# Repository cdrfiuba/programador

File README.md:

# Programador del Club de Robótica

El club cuenta con varios programadores ISP.

Cada programador cuenta con dos conexiones:
* Target (targ)
    - La conexión más usada. Sirve para programar un microcontrolador externo.
* ISP
    - Sirve para programar el programador (usualmente usando otro programador del club).
      De esta forma un programador sirve para crear más programadores.

## Conexiones

Cada puerto cuenta con 6 pines conectados a un cable plano:

- VCC (usualmente +5V que vienen de la conexión USB)
- GND
- SCK Señal de clock.
- RESET Permite "apagar" el microcontrolador y programarlo por SPI. De esa forma los demás pines pueden ser usados para otras tareas cuando el microcontrolador no está siendo programado.
- MISO (master-in slave-out)<sup>1</sup> Datos del microcontrolador al programador.
- MOSI (master-out slave-in)<sup>1</sup> Datos del programador al microcontrolador.

<sup>1 Nota: SIMO y SOMI suelen ser nombres más simpáticos pero menos usados.</sup>

La ubicación de cada pin en el puerto se muestra a continuación

## [Wiki](https://github.com/cdrfiuba/programador/wiki)

En la [Wiki](https://github.com/cdrfiuba/programador/wiki) de este repositorio se detalla la construcción de un programador como su uso.

- [Programador del Club de Robótica](https://github.com/cdrfiuba/programador/wiki#programador-del-club-de-rob%C3%B3tica)
  - [¿Cómo armar el programador?](https://github.com/cdrfiuba/programador/wiki#c%C3%B3mo-armar-el-programador)
    - [Versión 1.8](https://github.com/cdrfiuba/programador/wiki#versi%C3%B3n-18)
    - [Versión 1.7](https://github.com/cdrfiuba/programador/wiki#versi%C3%B3n-17)
    - [Versión 1.6](https://github.com/cdrfiuba/programador/wiki#versi%C3%B3n-16)
  - [Lista de Materiales](https://github.com/cdrfiuba/programador/wiki#lista-de-materiales)
    - [Versión 1.6 a 1.8:](https://github.com/cdrfiuba/programador/wiki#versi%C3%B3n-16-a-18)
      - [Lista de materiales a soldar](https://github.com/cdrfiuba/programador/wiki#lista-de-materiales-a-soldar)
      - [Lista de materiales para comprar](https://github.com/cdrfiuba/programador/wiki#lista-de-materiales-para-comprar)
    - [Versión 1.5 o anteriores](https://github.com/cdrfiuba/programador/wiki#versi%C3%B3n-15-o-anteriores)
    - [¿Qué firmware debe llevar mi programador?](https://github.com/cdrfiuba/programador/wiki#qu%C3%A9-firmware-debe-llevar-mi-programador)
    - [Programar el microcontrolador del programador.](https://github.com/cdrfiuba/programador/wiki#programar-el-microcontrolador-del-programador)
    - [¿Cómo armar el conector para programar tu microcontrolador?](https://github.com/cdrfiuba/programador/wiki#c%C3%B3mo-armar-el-conector-para-programar-tu-microcontrolador)
      - [Configuración. Solución a problemas comunes](https://github.com/cdrfiuba/programador/wiki#configuraci%C3%B3n-soluci%C3%B3n-a-problemas-comunes)
      - [No tengo permisos para acceder al dispositivo (Linux)](https://github.com/cdrfiuba/programador/wiki#no-tengo-permisos-para-acceder-al-dispositivo-linux)
      - [Microcontrolador no reconocido.](https://github.com/cdrfiuba/programador/wiki#microcontrolador-no-reconocido)
      - [Para el ATtiny4313](https://github.com/cdrfiuba/programador/wiki#para-el-attiny4313)
      - [Para el ATmega88PA que adquirimos recientemente](https://github.com/cdrfiuba/programador/wiki#para-el-atmega88pa-que-adquirimos-recientemente)
- [Windows necesita un driver](https://github.com/cdrfiuba/programador/wiki#windows-necesita-un-driver)
  - [Licencias](https://github.com/cdrfiuba/programador/wiki#licencias)
  - [Hojas de datos](https://github.com/cdrfiuba/programador/wiki#hojas-de--datos)
  - [Archivos de fabricación](https://github.com/cdrfiuba/programador/wiki#archivos-de-fabricaci%C3%B3n)
- [Fabricantes](https://github.com/cdrfiuba/programador/wiki/Fabricantes)
- [Introducción súper básica a los microcontroladores](https://github.com/cdrfiuba/programador/wiki/Programaci%C3%B3n-de-microcontroladores-AVR-en-C)
- [Quemar un bootloader de Arduino](https://github.com/cdrfiuba/programador/wiki/Quemar-un-bootloader-de-Arduino)

## Pequeña guía para programar un microcontrolador externo

Se utiliza el microcontrolador `ATMEGA168A` a modo de ejemplo (ya que el club cuenta con varios).

La siguiente guía asume el uso de un oscilador externo, si bien el microcontrolador puede ser programador utilizando su oscilador interno.

Se conecta al microcontrolador como muestra la siguiente figura. El valor ideal de los capacitores conectados al cristal se detalla en la hoja de datos del microcontrolador. Para este microcontrolador los capacitores recomendados son de 12pF a 22pF. El capacitor de desacople no es requerido pero es siempre una buena idea agregar uno.

Asumiendo que se utiliza un cristal de 16 MHz se crea un archivo `main.c` con el siguiente código:

```C
#include <avr/io.h>
#define F_CPU 16000000UL  // Corresponde a 16 MHz
#include <util/delay.h>

int main (void) {
  DDRC |= _BV(DDC3);  // Se setea el pin 26 como salida

  while(1) {
      PORTC |= _BV(PC3);  // Se prende el pin 26

      _delay_ms(1); // Se espera un milisegundo

      PORTC &= ~_BV(PC3);  // Se apaga el pin 26

      _delay_ms(1);  // Se espera otro milisegundo
  }

  return 1;
}
```

Este código produce una onda cuadrada de 500Hz a la salida del pin 26.

Para programadorlo se crea el siguiente script `programar.sh`

```bash
#!/usr/bin/env sh

# Compilación del programa
avr-gcc -Os -mmcu=atmega168a -c -o main.o main.c
avr-gcc -Os -mmcu=atmega168a -o main.elf main.o
avr-objcopy -O ihex -R .eeprom main.elf main.hex

# Cargar el programa en el microcontrolador
avrdude -v -p m168 -c usbtiny -U flash:w:main.hex

# Limpieza de los archivos generados
rm main.o main.hex main.elf
```

A su vez se crea un script `fusibles.sh` para setear los fuses del microcontrolador
Si bien se puede obtener el valor de los fusibles a mano, existen páginas que ya hacen este trabajo.
Una posible página es https://www.engbedded.com/fusecalc
Esta página además posee la ventaja de darnos los flags para el comando de `avrdude`.

```bash
#!/usr/bin/env bash

avrdude -v -p m168 -c usbtiny -U lfuse:w:0xce:m -U hfuse:w:0xdf:m -U efuse:w:0xf9:m
```

Se da permiso de ejecución a ambos scripts por única vez
```console
$ chmod +x programar.sh
$ chmod +x fusibles.sh
```

Se setean los fusibles por única vez. Puede correrse también en el futuro si, por ejemplo, se desea dividir la cuenta del clock por 8, o utilizar el oscilador interno u otras razones. Pero ha de tenerse en cuenta que se debe modificar el script.

```console
$ ./fusibles.sh
```

Se programa el microcontrolador

```console
$ ./programar.sh
```

Ahora puede corroborarse que a la salida del pin 26 hay una onda cuadrada de 500Hz.

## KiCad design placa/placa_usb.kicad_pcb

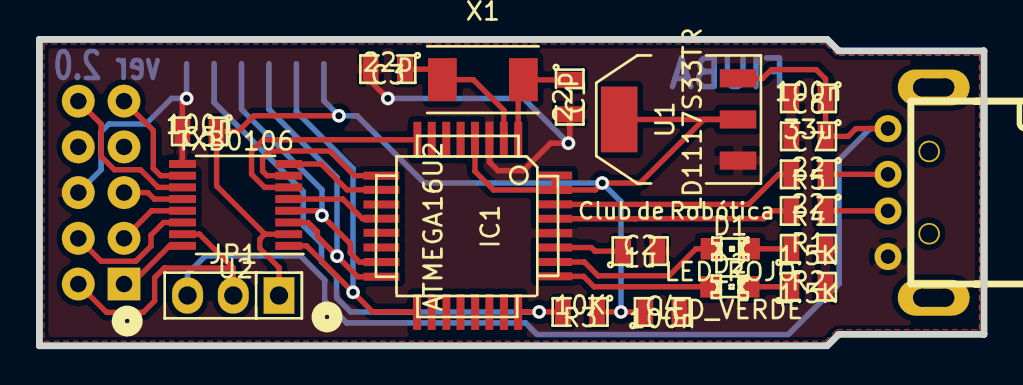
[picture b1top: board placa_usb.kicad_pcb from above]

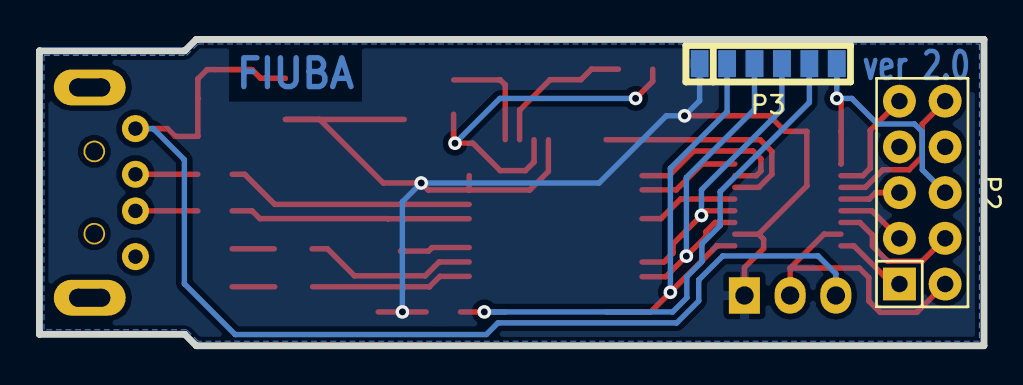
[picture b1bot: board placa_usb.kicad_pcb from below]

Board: 2 copper layers, 52.5 x 17.0 mm, 22 parts (2 on the bottom side), 29 nets.

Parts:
C1, C3: 22p; SMD-0805
C2: 1u; SMD-0805
C4, C5, C6: 100n; SMD-0805
C7: 33u; SMD-0805
D1: LED_ROJO; LED-0805
D2: LED_VERDE; LED-0805
IC1: ATMEGA16U2; TQFP-32
JP1: JUMPER3; Socket_Strip_Straight_1x03
P1: USB_A; USB_A_custom
P2: CONN_02X05; Socket_Strip_Straight_2x05
P3: CONN_01X06; Socket_Strip_smd_1x06
R1, R2: 1.5K; SMD-0805
R3: 10K; SMD-0805
R4, R5: 22; SMD-0805
U1: LD1117S33TR; SOT-223
U2: TXB0106; TSSOP-16_4.4x5mm_Pitch0.65mm
X1: 8MHz; Crystal_SMD_0603_2Pads_obsolete

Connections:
+3V3: C4.1, C5.1, IC1.4, IC1.31, IC1.32, JP1.1, P3.1, R3.1, U1.2, U2.2
+5V: C6.1, C7.1, JP1.3, P1.1, U1.3
/D+: IC1.29, R4.2
/D-: IC1.30, R5.2
/Enable: IC1.10, U2.8
/MISO: IC1.17, P3.2, U2.1
/MISO-O: P2.1, U2.16
/MOSI: IC1.16, P3.3, U2.3
/MOSI-O: P2.4, U2.14
/RESET: IC1.24, P3.5, R3.2
/RST: IC1.12, U2.5
/RST-O: P2.5, U2.12
/RX: IC1.8, U2.6
/RX-O: P2.10, U2.11
/Rojo: D1.1, IC1.26
/SCK: IC1.15, P3.4, U2.4
/SCK-O: P2.3, U2.13
/TX: IC1.9, U2.7
/TX-O: P2.9, U2.10
/VCC-O: JP1.2, P2.2, U2.15
/Verde: D2.1, IC1.25
GND: C1.2, C2.2, C3.2, C4.2, C5.2, C6.2, C7.2, IC1.3, IC1.28, P1.4, P2.6, P3.6, R1.2, R2.2, U1.1, U2.9
unnamed: C1.1, IC1.1, X1.2
unnamed: C2.1, IC1.27
unnamed: C3.1, IC1.2, X1.1
unnamed: D1.2, R1.1
unnamed: D2.2, R2.1
unnamed: P1.2, R5.1
unnamed: P1.3, R4.1

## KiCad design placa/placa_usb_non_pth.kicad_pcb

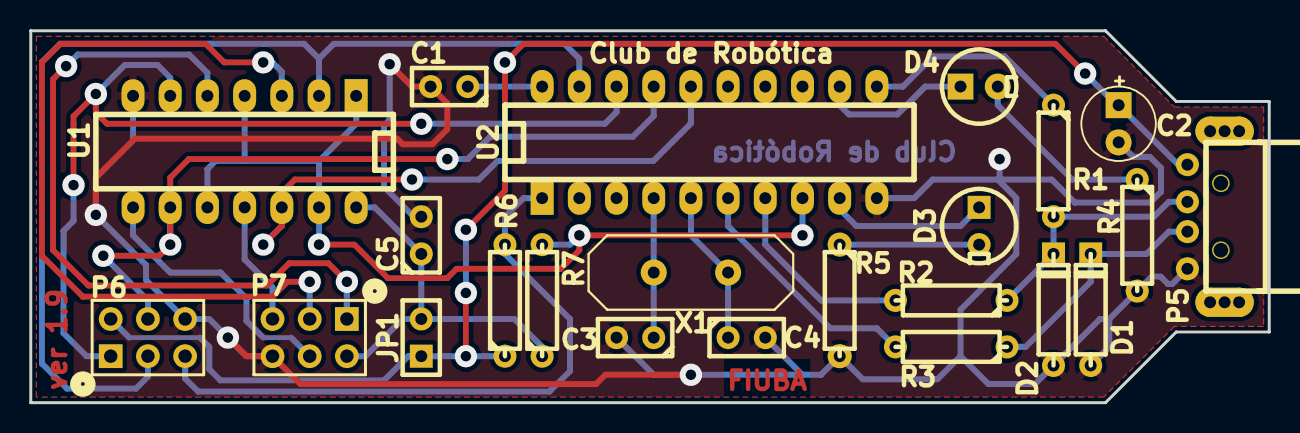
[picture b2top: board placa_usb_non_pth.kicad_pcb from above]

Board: 2 copper layers, 84.6 x 25.4 mm, 23 parts (0 on the bottom side), 24 nets.

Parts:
C1, C5: 100n; C1
C2: 100u; C1V5
C3, C4: 22p; C1
D1, D2: 3.6V; D3
D3: LED_VERDE; LEDV
D4: LED_ROJO; LEDV
JP1: VCC; SIL-2
P5: USB_A; USB_A_custom
P6: ISP; pin_array_3x2
P7: Targ.; pin_array_3x2
R1, R4, R5: 1.5K; R3-LARGE_PADS
R2, R3: 27; R3-LARGE_PADS
R6: 10K; R3-LARGE_PADS
R7: 470k; R3-LARGE_PADS
U1: 74HC125N; 14DIP-ELL300
U2: ATTINY2313DIP/SO; DIP-20__300_ELL
X1: 12MHz; HC-18UV

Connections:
+5V: C1.1, C2.1, JP1.1, P5.1, P6.2, R6.1, U2.20
/Enable: R7.2, U1.1, U1.4, U1.10, U1.13, U2.8
/MISO: P6.1, U1.6, U2.18
/MOSI: P6.4, U1.9, U2.17
/PD2: R3.2, U2.6
/PD3: R2.2, U2.7
/PD6: R1.1, U2.11
/RST: P6.5, R6.2, U2.1
/RST_B: U1.12, U2.16
/Rojo: D4.1, U2.12
/SCK: P6.3, U1.2, U2.19
/Verde: D3.1, U2.9
GND: C1.2, C2.2, C3.2, C4.2, C5.2, D1.1, D2.1, P5.4, P6.6, P7.6, R4.2, R5.2, U1.7, U2.10
unnamed: D4.2, R4.1
unnamed: D3.2, R5.1
unnamed: P7.5, U1.11
unnamed: C3.1, U2.4, X1.1
unnamed: C4.1, U2.5, X1.2
unnamed: D1.2, P5.3, R3.1
unnamed: D2.2, P5.2, R1.2, R2.1
unnamed: P7.3, U1.3
unnamed: P7.4, U1.8
unnamed: P7.1, U1.5
VCC: C5.1, JP1.2, P7.2, R7.1, U1.14

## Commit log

2008-07-09 Initial import
2008-07-09 Cambiamos usb_setup para que sean elseif 2014 bytes.
2008-07-09 Saco algunos archivos
2008-07-09 Cambio el if por un case en usb_setup
2008-07-09 Agregamos la opcion para invertir el sck. Sacamos el port y el echo.
2008-07-09 Borro el main.hex del darcs
2008-07-11 Lectura en rafaga intento 1
    Ahora puede recibir en rafaga las lecturas y escrituras,. No esta
    probado. Tuve que comentar el invertir SCK para que entre.
2008-07-11 Intente agregar modo rafaga 8051 El AVR anda como antes, pero el modo rafaga no anda con el 8253. hace cualquier cosa. Sin ideas por ahora.
2008-07-14 funciona modo rafaga con el 8253
2008-07-15 Funciona el tamanio como argumento de spi_rw. COMENTE una de las funciones de USB para ganar espacio.
2008-07-19 Agrego esqueleto de documentacion en latex.
2008-07-19 Agregue lo que habia escrito en texto plano. se ve FEO, no se latex. BU :(
2008-08-20 Changed some absolute paths to relative.
2008-09-29 Agrego ultimo PCB, falta el nuevo conector USB.
2008-10-23 Borro el archivo conector_usb.mod
2008-11-21 agrego el Makefile que faltaba
2009-03-21 Sacamos el plano de tierra y escribimos FIUBA en el pcb.
2009-04-14 Arreglo el texto que pego gabriel en el tex.
2010-08-31 Creo un directorio para la placa, para que quede mas ordenado.
2010-09-12 Saco el jumper de alimentacion del buffer que no servia para nada.
2010-09-14 Modifico el esquematio: * Saco el jumper de Puerto a Vcc (el de Vcc a buffer ya lo habia sacado) * Cambio los conectores de 5x2 por los de 3x2 * Agrego una R de pull up de 470K en el enable del buffe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
2010-09-14 Actualizo la asignacion de componentes por los ultimos cambios en el esquematico.
2010-10-16 Correccion en el esquematico, y placa doble faz. Falta texto en la placa
2010-10-16 Arregle un par de pistas, la serigrafia, y agregue texto del club
2010-10-16 Cambio los textos de los conectores y el jumper.
2010-10-16 Vuelvo a cambiar los textos y pongo un punto marcando el 1 de los conectores.
2010-10-16 Agrego titulo, version, autor y licencia a las propiedades de la hoja del pcb.
2010-10-19 Pase el texto a la capa de serigrafia y agrande los 'puntos' en los conectores 3x2
2010-10-20 Agregue el numero de version 1.5
2010-10-20 Peque?os cambios a la capa de serigrafia. Movi un par de cartelitos.
2010-10-21 Added tag PCB_ver_1.5 for changeset 7cba149e0b5b
2010-10-21 Version 1.6. Agregamos capacitor de alimentacion y se adecuo el impreso a las especificaciones de Mayer
2010-10-21 Added tag PCB_ver_1.6 for changeset f48b9e476b3c
2010-10-27 Cambio la licencia en el esquematico porque estaba mal.
2010-11-27 Agrego el main.hex, que es el firmware
2010-11-28 modifique el esquematico para hacer mas claro el conector usb. cree el componente con las etiquetas correctas
2010-11-28 Arregle el problema del usb invertido en el board. Version 1.7
2010-11-28 Correcciones finales a la version 1.7. Se agrega el archivo .lst que tiene la lista de materiales
2010-11-28 Added tag Version 1.7 for changeset 1fb529737f96
2010-12-02 Removed tag Version 1.7
2010-12-02 Elimine una conexion innecesaria de Vcc.
2010-12-02 Added tag PCB_ver_1.7 for changeset fec1d2a1ccf3
2010-12-06 Actualizacion de las bibliotecas de componentes USB
2010-12-06 Archivos de las bibliotecas, que no parecen utilies pero el kicad se queja si faltan
2010-12-06 Adaptador para Conector miniUSB para corregir el error del PCB_ver_1.6
2010-12-09 - Agregue las hojas de datos - Junte todo en una carpeta para trabajar con el avrstudio - Cree un archivo para trabajar solo con el 8253
2010-12-10 Graba el test del 8253! Peeeeeero, solo si compilo sin ninguna optimizacion. Si pongo Os (por tama?o) hace cualquier cosa, ni siquiera sube la linea de reset.
2010-12-11 Para poder compilar con el avrstudio, tuve que reescribir el label del vector de interrupcion externa 0. No estaba haciendo la llamada a la rutina de usb.s donde correspondia (en el flanco ascendente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
2011-04-03 No graba el test del s52 :( Probe de todo. Copiar otros programadores Ir paso a paso Etc
2011-04-03 Agrego los archivos que faltaban
2011-04-03 Ronombro carpeta donde ejecuto el codigo para testeo
2011-04-04 Creo la carpeta y el proyecto para tener un firmware que funcione con el 8253
2011-04-04 - La version del AvrStudio NO pudo enumerar el USB :( - Creo otra carpeta con la estructura original y le agrego los cambios a main.c
    Funciono!!!!!!
    Esta version SOLO GRABA EL AT89S8253, ningun otro micro (ni AVR, ni otros)
2011-04-30 Muevo las pistas que pasan por entre medio de los conectores de 2x3 y agrando los pads de los mismos.
2011-04-30 Added tag Versi?n 1.7.1 for changeset 4f13b5f8753d
2011-05-02 agrande 2 agujeros mas
2011-05-02 Added tag Version 1.8 enviada a mayer for changeset ee686fabf2b8
2011-05-02 Gerber generados
2011-05-02 Added tag Version 1.8 enviada a mayer (ahora si) for changeset 651e15ddcdc9
2011-05-17 Creo un nuevo branch con el c?digo actualizado del programador. Cambio nombre del directorio de codigo a usbtinyisp porque me parecio m?s apropiado.
2011-09-16 Pre sync
2011-09-17 Se empiezan a implementar los punteros a funciones. La idea es segun el protocolo a usar se apunte el puntero a la funcion correspondiente.
    Hay que tratar de usar los punteros lo menos posible ya que consumen mucho
    espacio en memoria.
2011-10-14 Agrego el proyecto para AVRStudio 5.0 y creo otro set de archivos sobre los que trabajar
2013-06-15 Muevo todo para convertir esta version en la unica
2013-06-16 Terminado para 8253, aunque no funciona (algunas cosas del main estan hardcodeadas). Si pongo para compilar para 4313 en lugar de 2313, no funciona. No pone el vector de interrupciones en el lugar co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
2013-06-16 Vuelve a funcionar como antes (mal) pero ahora bien configurado el 4313. Un problema con la definicion del vector de interrupcion.
2013-06-17 Funciono el grabado del programa largo! Todavia esta hardcodeado la elecci?n del s8253.
2013-06-18 Agrego el proyecto de avrstudio 6 para que sea mas facil abrir el proyecto mas adelante
2013-06-18 Version con los dos protocolos. Funciona!! Se agrega el nuevo main.hex
2013-06-18 Agrego las hojas de datos para rapida referencia.
2013-06-19 Agrego un define con la version(no se usa para nada)
2013-07-23 elimino las R a la salida del buffer y conecto la alimentacion del buffer a la salida por el target
2013-07-23 agrego una version para hacer sin PTH, faltaria revisar la serigrafia
2013-07-23 arregle la serigrafia y corregi algunos detalles, mande a fabricar una
2013-07-23 Added tag PCB_ver_1.9 for changeset 5fc9af66bcd5
2013-08-09 Se corrige celigrafia LED, se agrega signo +.
    Versi?n enviada a fabricar.
2013-09-21 Arreglo la compilacion en Linux.
    El Makefile tenia mezclada la capitalizacion del archivo avr_spi.c/h
2013-09-21 Closes branch 1.x, it was merged to default.
2013-09-21 Remove old, unused 'juntada' folder.
2015-01-24 Plantilla con 4 placas de programador v1.8
2015-01-24 Added tag Version 1.8 plantilla enviada a SeedStudio for changeset 360eda65eee2
2015-01-24 Version de prueba de la placa 2.0 con micro smd
2018-10-09 Declare descr_device and descr_config as static const to satisfy gcc.
2022-08-20 Agregar una pequeña guía y documentación
2024-07-06 Agregar links a la Wiki para gente no acostumbrada a GitHub. Agregar documentación relacionada a quemar bootloader de Arduino
